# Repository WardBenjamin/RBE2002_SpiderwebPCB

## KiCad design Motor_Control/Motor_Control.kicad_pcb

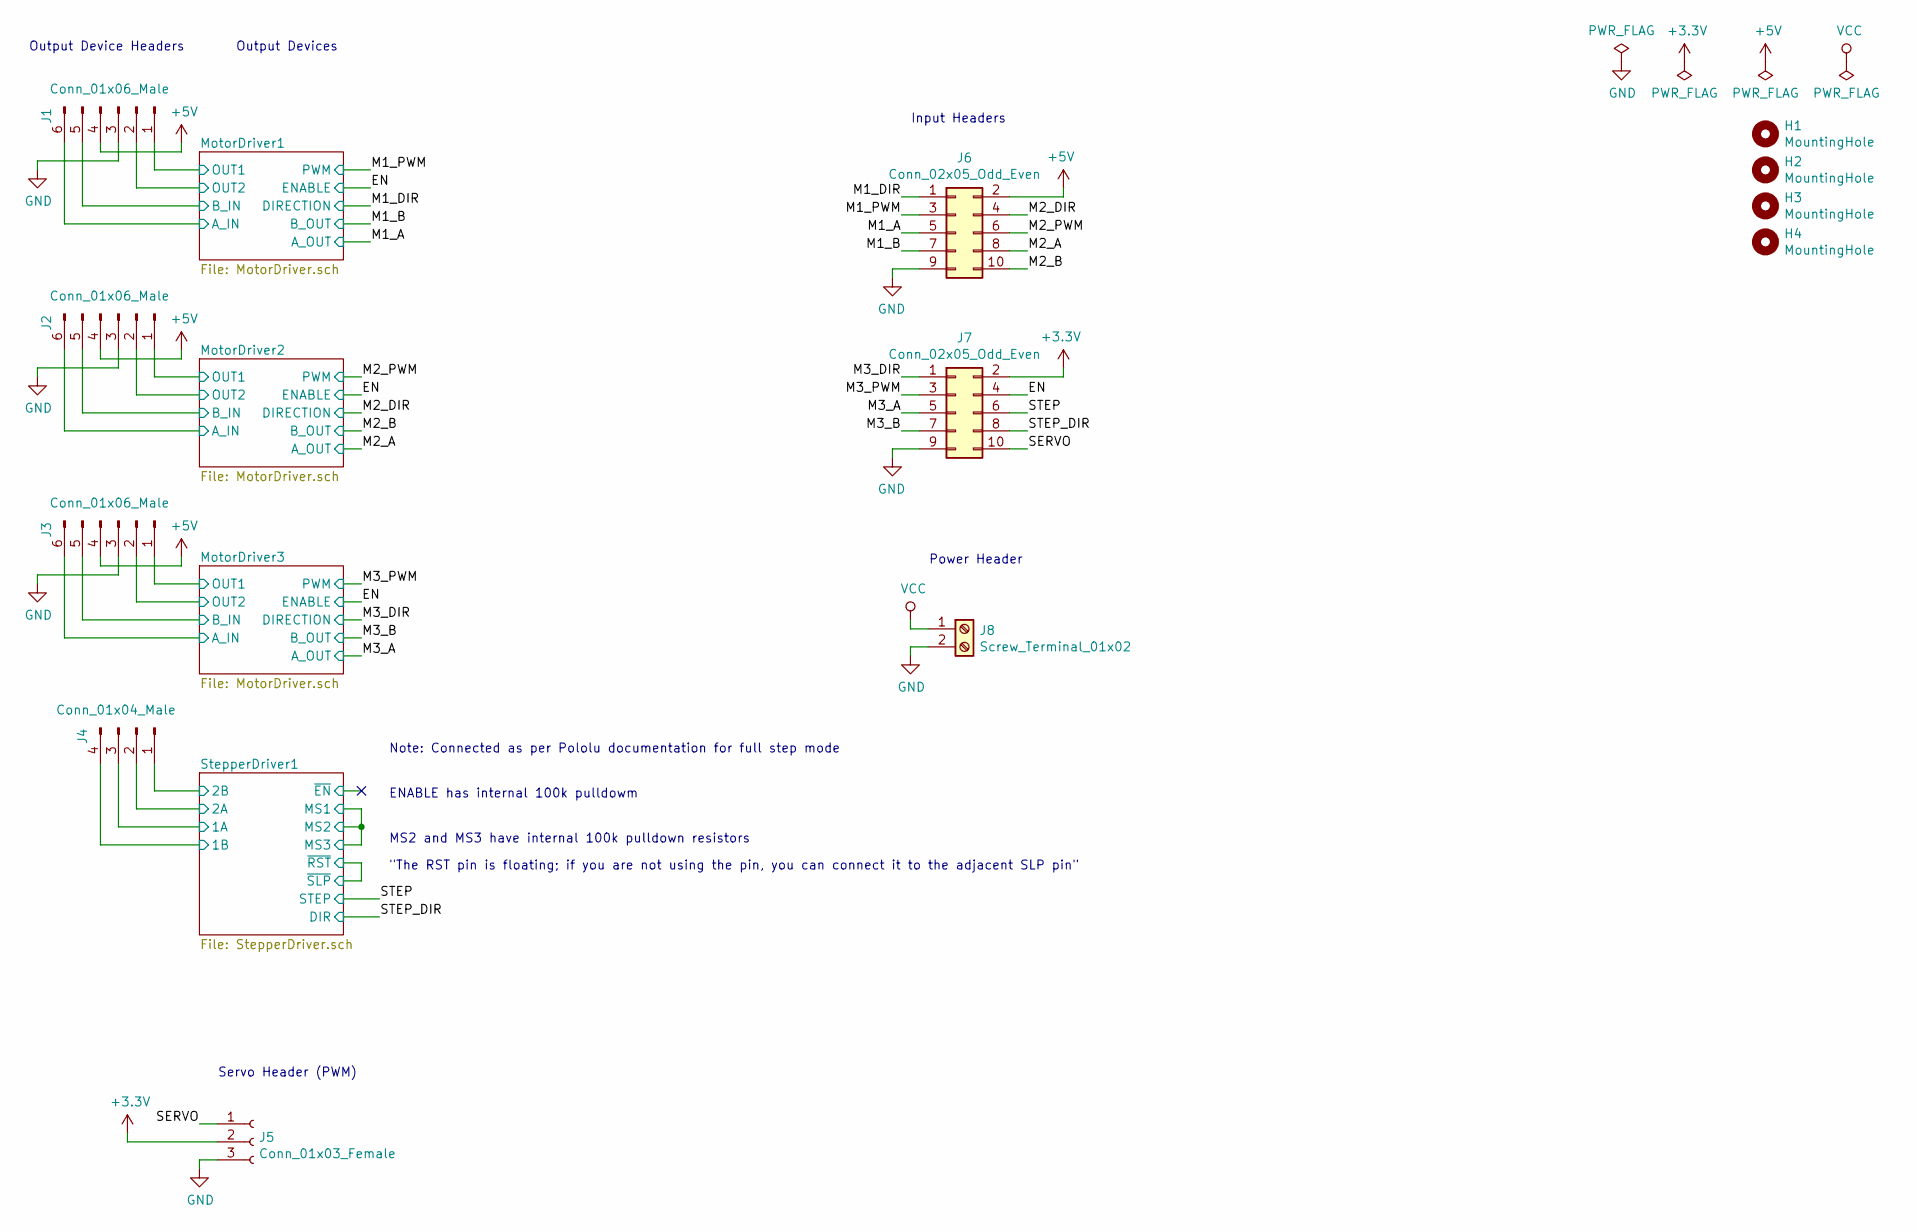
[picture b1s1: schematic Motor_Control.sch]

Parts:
H1, H2, H3, H4: MountingHole; MountingHole_3.2mm_M3
J1, J2, J3: Conn_01x06_Male; PinHeader_1x06_P2.54mm_Vertical
J4: Conn_01x04_Male; PinHeader_1x04_P2.54mm_Vertical
J5: Conn_01x03_Female; PinSocket_1x03_P2.54mm_Vertical
J6, J7: Conn_02x05_Odd_Even; PinSocket_2x05_P2.54mm_Vertical_SMD
J8: Screw_Terminal_01x02; PhoenixContact_MC_1,5_2-G-3.81_1x02_P3.81mm_Horizontal

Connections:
+3V3: J5.2, J7.2; also elsewhere on the board
+5V: J1.4, J2.4, J3.4, J6.2; also elsewhere on the board
/EN: J7.4; also elsewhere on the board
/M1_A: J6.5; also elsewhere on the board
/M1_B: J6.7; also elsewhere on the board
/M1_DIR: J6.1; also elsewhere on the board
/M1_PWM: J6.3; also elsewhere on the board
/M2_A: J6.8; also elsewhere on the board
/M2_B: J6.10; also elsewhere on the board
/M2_DIR: J6.4; also elsewhere on the board
/M2_PWM: J6.6; also elsewhere on the board
/M3_A: J7.5; also elsewhere on the board
/M3_B: J7.7; also elsewhere on the board
/M3_DIR: J7.1; also elsewhere on the board
/M3_PWM: J7.3; also elsewhere on the board
/MotorDriver1/A_IN: J1.6; also elsewhere on the board
/MotorDriver1/B_IN: J1.5; also elsewhere on the board
/MotorDriver1/OUT1: J1.1; also elsewhere on the board
/MotorDriver1/OUT2: J1.2; also elsewhere on the board
/MotorDriver2/A_IN: J2.6; also elsewhere on the board
/MotorDriver2/B_IN: J2.5; also elsewhere on the board
/MotorDriver2/OUT1: J2.1; also elsewhere on the board
/MotorDriver2/OUT2: J2.2; also elsewhere on the board
/MotorDriver3/A_IN: J3.6; also elsewhere on the board
/MotorDriver3/B_IN: J3.5; also elsewhere on the board
/MotorDriver3/OUT1: J3.1; also elsewhere on the board
/MotorDriver3/OUT2: J3.2; also elsewhere on the board
/SERVO: J5.1, J7.10
/STEP: J7.6; also elsewhere on the board
/STEP_DIR: J7.8; also elsewhere on the board
/StepperDriver1/1A: J4.3; also elsewhere on the board
/StepperDriver1/1B: J4.4; also elsewhere on the board
/StepperDriver1/2A: J4.2; also elsewhere on the board
/StepperDriver1/2B: J4.1; also elsewhere on the board
GND: J1.3, J2.3, J3.3, J5.3, J6.9, J7.9, J8.2; also elsewhere on the board
VCC: J8.1; also elsewhere on the board

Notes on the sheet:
ENABLE has internal 100k pulldowm
MS2 and MS3 have internal 100k pulldown resistors
"The RST pin is floating; if you are not using the pin, you can connect it to the adjacent SLP pin"
Output Device Headers
Servo Header (PWM)
Output Devices
Input Headers
Note: Connected as per Pololu documentation for full step mode
Power Header

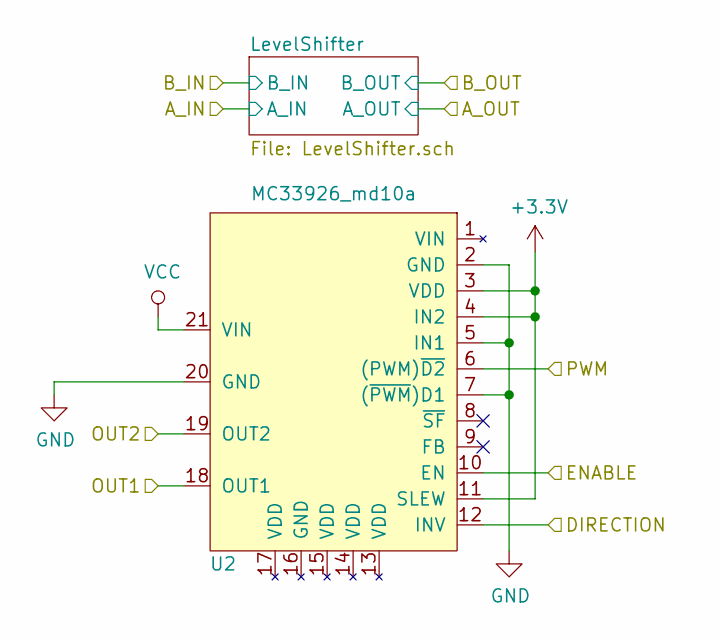
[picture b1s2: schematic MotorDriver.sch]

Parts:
U1: MC33926_md10a

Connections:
+3V3: U1.3 (VDD), U1.4 (IN2), U1.11 (SLEW); also elsewhere on the board
/EN: U1.10 (EN); also elsewhere on the board
/M1_DIR: U1.12 (INV); also elsewhere on the board
/M1_PWM: U1.6 ((PWM)~D2); also elsewhere on the board
/MotorDriver1/OUT1: U1.18 (OUT1); also elsewhere on the board
/MotorDriver1/OUT2: U1.19 (OUT2); also elsewhere on the board
GND: U1.2 (GND), U1.5 (IN1), U1.7 ((~PWM~)D1), U1.20 (GND); also elsewhere on the board
VCC: U1.21 (VIN); also elsewhere on the board

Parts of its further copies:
U2, U3: MC33926_md10a

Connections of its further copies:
+3V3: U2.3 (VDD), U2.4 (IN2), U2.11 (SLEW), U3.3 (VDD), U3.4 (IN2), U3.11 (SLEW); also elsewhere on the board
/EN: U2.10 (EN), U3.10 (EN); also elsewhere on the board
/M2_DIR: U2.12 (INV); also elsewhere on the board
/M2_PWM: U2.6 ((PWM)~D2); also elsewhere on the board
/M3_DIR: U3.12 (INV); also elsewhere on the board
/M3_PWM: U3.6 ((PWM)~D2); also elsewhere on the board
/MotorDriver2/OUT1: U2.18 (OUT1); also elsewhere on the board
/MotorDriver2/OUT2: U2.19 (OUT2); also elsewhere on the board
/MotorDriver3/OUT1: U3.18 (OUT1); also elsewhere on the board
/MotorDriver3/OUT2: U3.19 (OUT2); also elsewhere on the board
GND: U2.2 (GND), U2.5 (IN1), U2.7 ((~PWM~)D1), U2.20 (GND), U3.2 (GND), U3.5 (IN1), U3.7 ((~PWM~)D1), U3.20 (GND); also elsewhere on the board
VCC: U2.21 (VIN), U3.21 (VIN); also elsewhere on the board

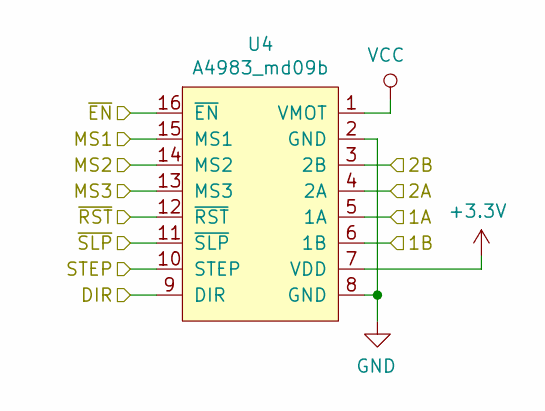
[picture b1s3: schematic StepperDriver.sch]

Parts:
U4: A4983_md09b

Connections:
+3V3: U4.7 (VDD); also elsewhere on the board
/STEP: U4.10 (STEP); also elsewhere on the board
/STEP_DIR: U4.9 (DIR); also elsewhere on the board
/StepperDriver1/1A: U4.5 (1A); also elsewhere on the board
/StepperDriver1/1B: U4.6 (1B); also elsewhere on the board
/StepperDriver1/2A: U4.4 (2A); also elsewhere on the board
/StepperDriver1/2B: U4.3 (2B); also elsewhere on the board
/StepperDriver1/MS1: U4.13 (MS3), U4.14 (MS2), U4.15 (MS1)
/StepperDriver1/~EN: U4.16 (~EN)
/StepperDriver1/~RST: U4.11 (~SLP), U4.12 (~RST)
GND: U4.2 (GND), U4.8 (GND); also elsewhere on the board
VCC: U4.1 (VMOT); also elsewhere on the board

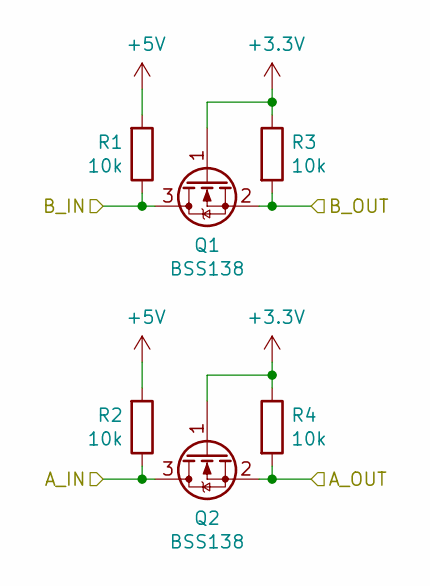
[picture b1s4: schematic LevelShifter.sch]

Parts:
Q1, Q2: BSS138; SOT-23
R1, R2, R3, R4: 10k; R_0603_1608Metric_Pad1.05x0.95mm_HandSolder

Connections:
+3V3: Q1.1 (G), Q2.1 (G), R3.1, R4.1; also elsewhere on the board
+5V: R1.2, R2.2; also elsewhere on the board
/M1_A: Q2.2 (S), R4.2; also elsewhere on the board
/M1_B: Q1.2 (S), R3.2; also elsewhere on the board
/MotorDriver1/A_IN: Q2.3 (D), R2.1; also elsewhere on the board
/MotorDriver1/B_IN: Q1.3 (D), R1.1; also elsewhere on the board

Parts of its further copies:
Q3, Q4, Q5, Q6: BSS138; SOT-23
R5, R6, R7, R8, R9, R10, R11, R12: 10k; R_0603_1608Metric_Pad1.05x0.95mm_HandSolder

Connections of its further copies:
+3V3: Q3.1 (G), Q4.1 (G), Q5.1 (G), Q6.1 (G), R7.1, R8.1, R11.1, R12.1; also elsewhere on the board
+5V: R5.2, R6.2, R9.2, R10.2; also elsewhere on the board
/M2_A: Q4.2 (S), R8.2; also elsewhere on the board
/M2_B: Q3.2 (S), R7.2; also elsewhere on the board
/M3_A: Q6.2 (S), R12.2; also elsewhere on the board
/M3_B: Q5.2 (S), R11.2; also elsewhere on the board
/MotorDriver2/A_IN: Q4.3 (D), R6.1; also elsewhere on the board
/MotorDriver2/B_IN: Q3.3 (D), R5.1; also elsewhere on the board
/MotorDriver3/A_IN: Q6.3 (D), R10.1; also elsewhere on the board
/MotorDriver3/B_IN: Q5.3 (D), R9.1; also elsewhere on the board

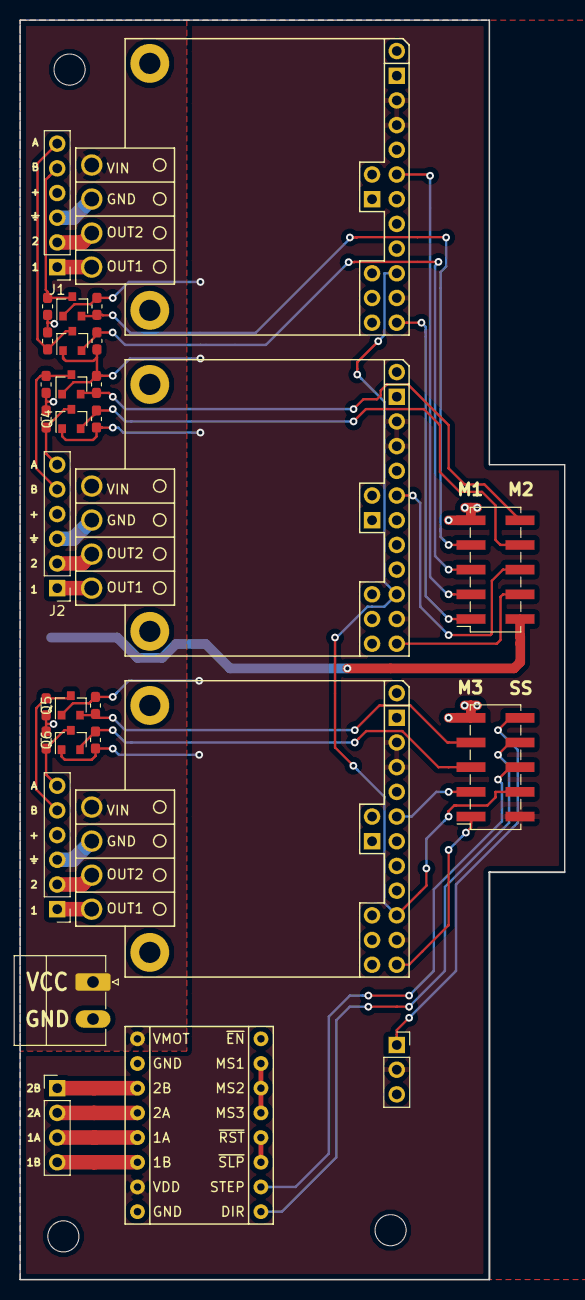
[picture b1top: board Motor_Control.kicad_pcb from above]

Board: 2 copper layers, 56.0 x 129.5 mm, 33 parts (0 on the bottom side), 38 nets.

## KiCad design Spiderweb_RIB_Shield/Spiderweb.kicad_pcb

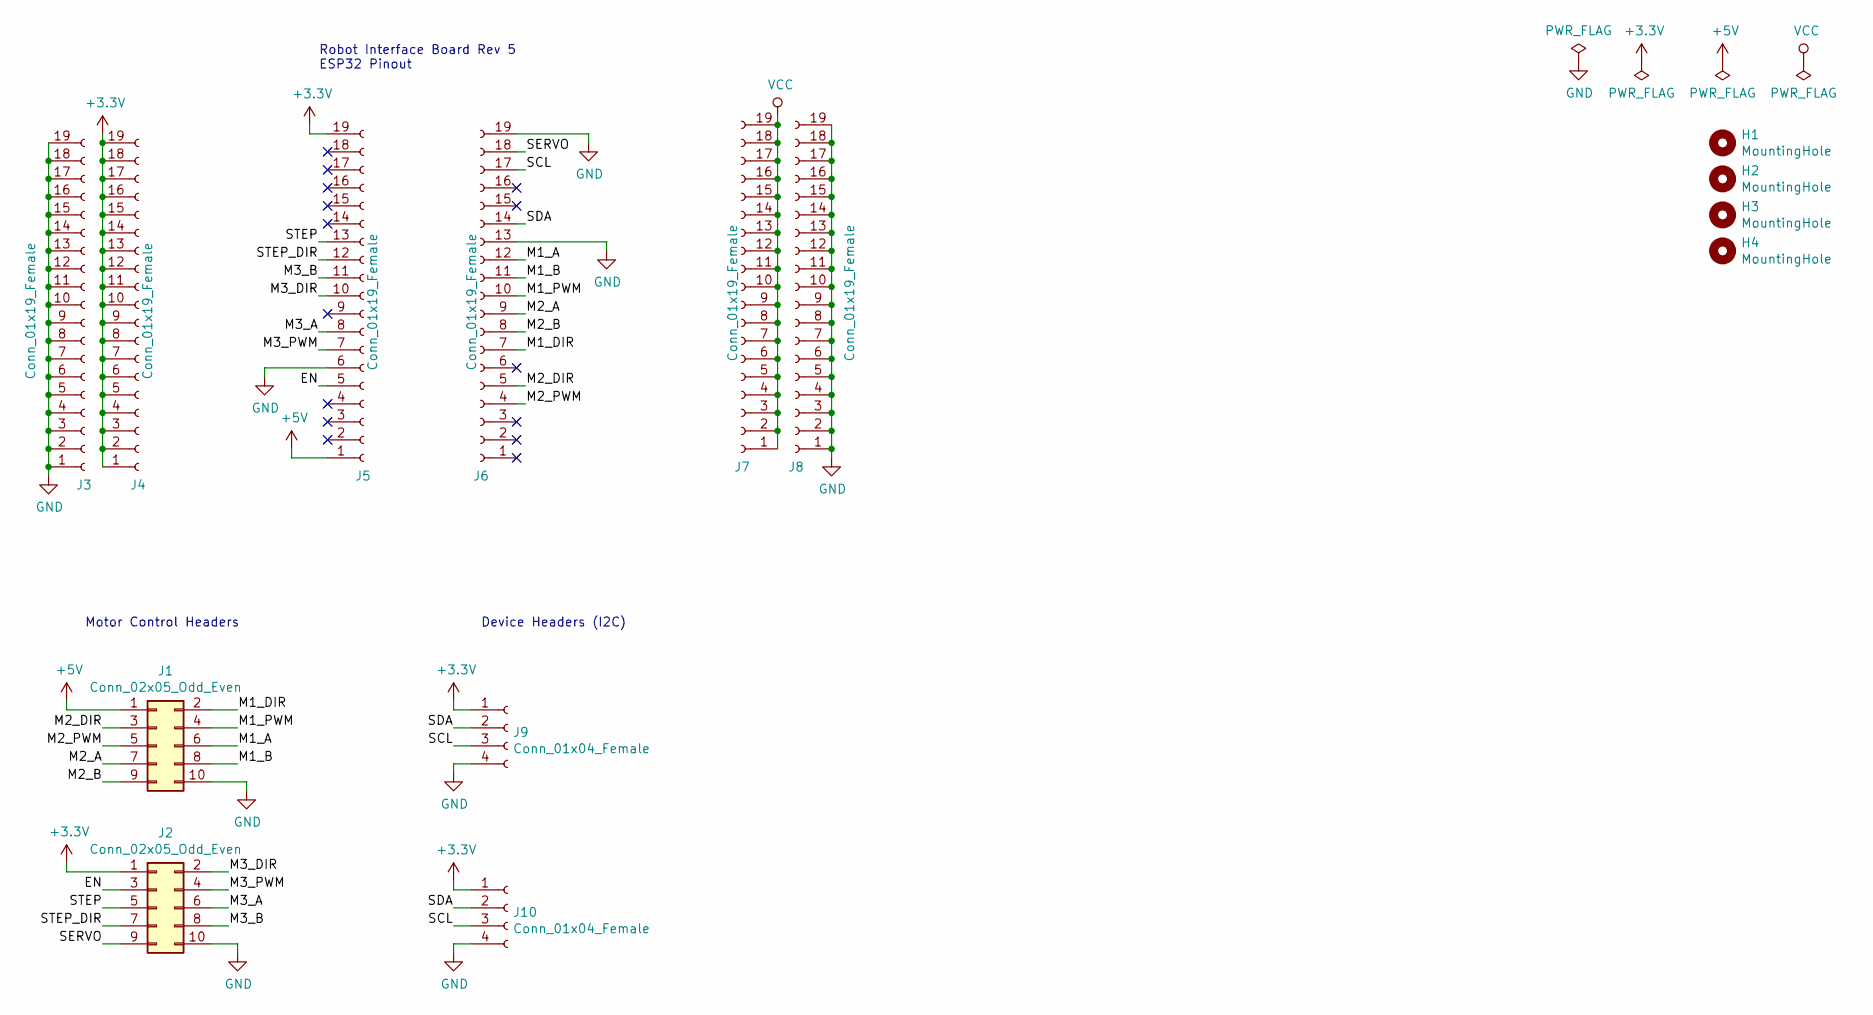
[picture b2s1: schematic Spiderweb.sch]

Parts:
H1, H2, H3, H4: MountingHole; MountingHole_4.3mm_M4
J1, J2: Conn_02x05_Odd_Even; PinHeader_2x05_P2.54mm_Vertical_SMD
J3, J4, J5, J6, J7, J8: Conn_01x19_Female; PinSocket_1x19_P2.54mm_Vertical
J9, J10: Conn_01x04_Female; PinSocket_1x04_P2.54mm_Vertical

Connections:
+3V3: J2.1, J4.1, J4.2, J4.3, J4.4, J4.5, J4.6, J4.7, J4.8, J4.9, J4.10, J4.11, J4.12, J4.13, J4.14, J4.15, J4.16, J4.17, J4.18, J4.19, J5.19, J9.1, J10.1
+5V: J1.1, J5.1
/EN: J2.3, J5.5
/M1_A: J1.6, J6.12
/M1_B: J1.8, J6.11
/M1_DIR: J1.2, J6.7
/M1_PWM: J1.4, J6.10
/M2_A: J1.7, J6.9
/M2_B: J1.9, J6.8
/M2_DIR: J1.3, J6.5
/M2_PWM: J1.5, J6.4
/M3_A: J2.6, J5.8
/M3_B: J2.8, J5.11
/M3_DIR: J2.2, J5.10
/M3_PWM: J2.4, J5.7
/SCL: J6.17, J9.3, J10.3
/SDA: J6.14, J9.2, J10.2
/SERVO: J2.9, J6.18
/STEP: J2.5, J5.13
/STEP_DIR: J2.7, J5.12
GND: J1.10, J2.10, J3.1, J3.2, J3.3, J3.4, J3.5, J3.6, J3.7, J3.8, J3.9, J3.10, J3.11, J3.12, J3.13, J3.14, J3.15, J3.16, J3.17, J3.18, J3.19, J5.6, J6.13, J6.19, J8.1, J8.2, J8.3, J8.4, J8.5, J8.6, J8.7, J8.8, J8.9, J8.10, J8.11, J8.12, J8.13, J8.14, J8.15, J8.16, J8.17, J8.18, J8.19, J9.4, J10.4
VCC: J7.1, J7.2, J7.3, J7.4, J7.5, J7.6, J7.7, J7.8, J7.9, J7.10, J7.11, J7.12, J7.13, J7.14, J7.15, J7.16, J7.17, J7.18, J7.19

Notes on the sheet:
Robot Interface Board Rev 5 ESP32 Pinout
Device Headers (I2C)
Motor Control Headers

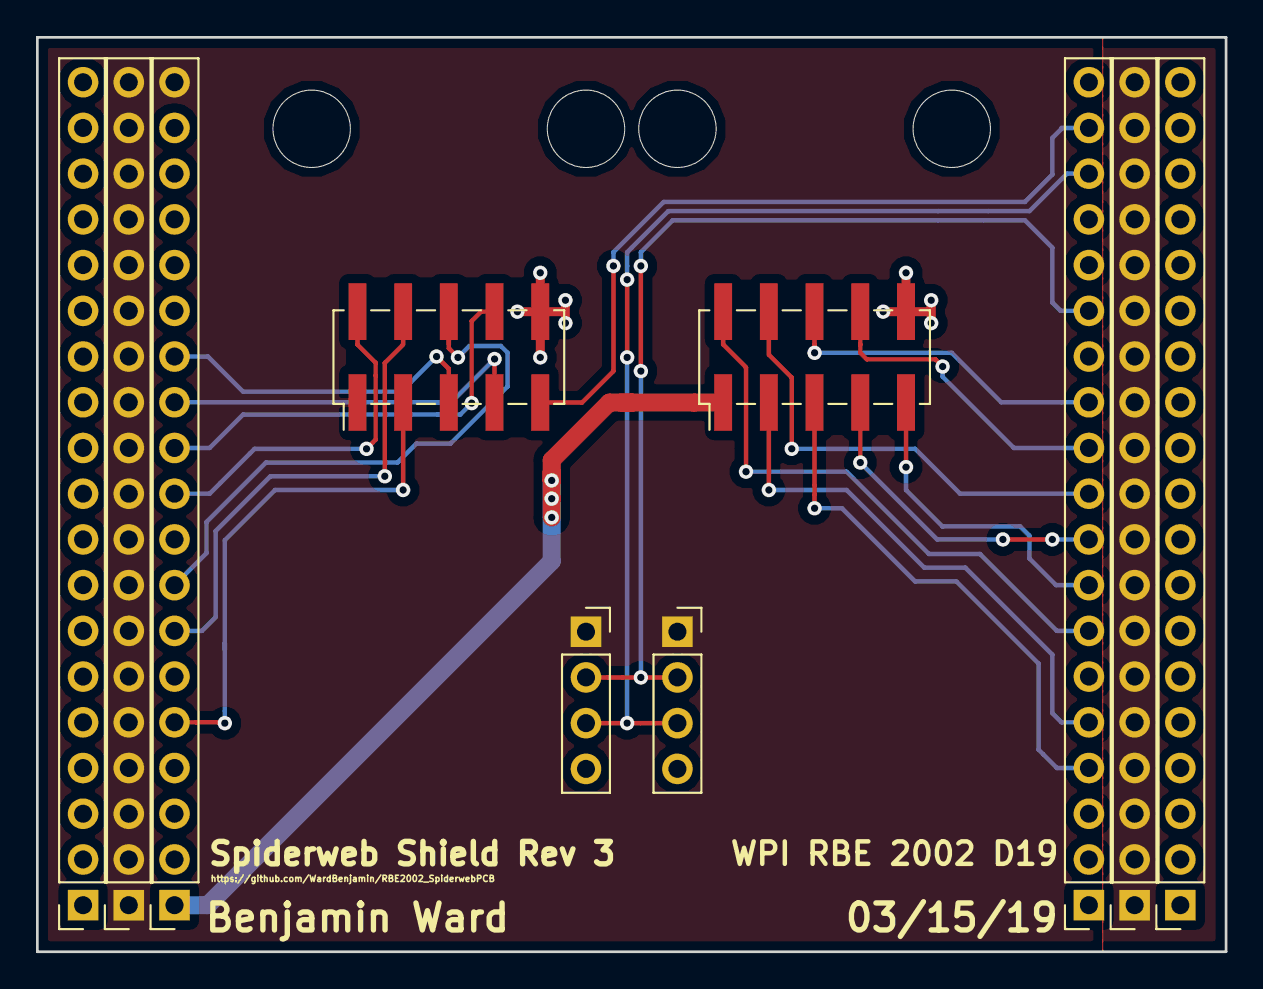
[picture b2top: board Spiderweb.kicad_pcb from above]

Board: 2 copper layers, 66.0 x 50.8 mm, 14 parts (0 on the bottom side), 22 nets.

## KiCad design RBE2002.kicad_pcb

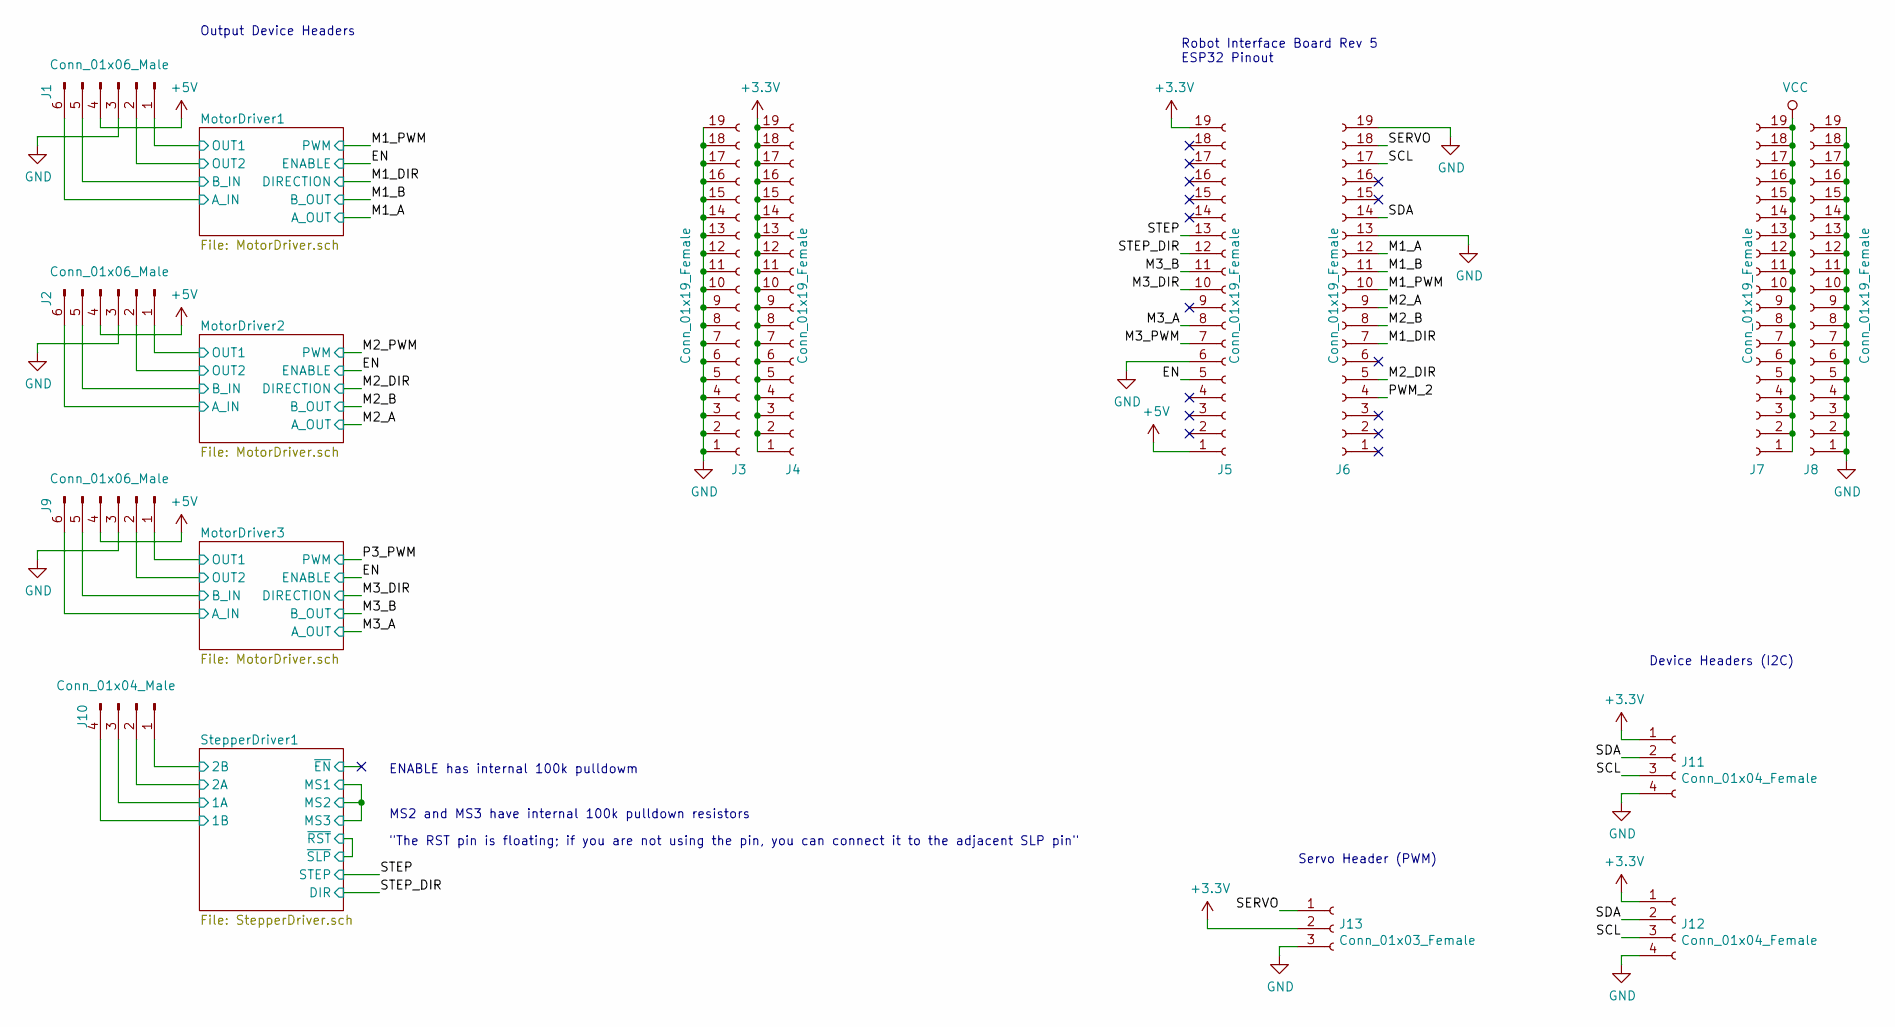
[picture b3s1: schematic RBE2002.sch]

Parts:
J1, J2, J9: Conn_01x06_Male; PinHeader_1x06_P2.54mm_Vertical
J3, J4, J5, J6, J7, J8: Conn_01x19_Female; PinSocket_1x19_P2.54mm_Vertical
J10: Conn_01x04_Male; PinHeader_1x04_P2.54mm_Vertical
J11, J12: Conn_01x04_Female; PinSocket_1x04_P2.54mm_Vertical
J13: Conn_01x03_Female; PinSocket_1x04_P2.54mm_Vertical

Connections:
+3V3: J4.1, J4.2, J4.3, J4.4, J4.5, J4.6, J4.7, J4.8, J4.9, J4.10, J4.11, J4.12, J4.13, J4.14, J4.15, J4.16, J4.17, J4.18, J4.19, J5.19, J11.1, J12.1, J13.2; also elsewhere on the board
+5V: J1.4, J2.4, J5.1, J9.4; also elsewhere on the board
/EN: J5.5; also elsewhere on the board
/M1_A: J6.12; also elsewhere on the board
/M1_B: J6.11; also elsewhere on the board
/M1_DIR: J6.7; also elsewhere on the board
/M1_PWM: J6.10; also elsewhere on the board
/M2_A: J6.9; also elsewhere on the board
/M2_B: J6.8; also elsewhere on the board
/M2_DIR: J6.5; also elsewhere on the board
/M3_A: J5.8; also elsewhere on the board
/M3_B: J5.11; also elsewhere on the board
/M3_DIR: J5.10; also elsewhere on the board
/M3_PWM: J5.7
/MotorDriver1/A_IN: J1.6; also elsewhere on the board
/MotorDriver1/B_IN: J1.5; also elsewhere on the board
/MotorDriver1/OUT1: J1.1; also elsewhere on the board
/MotorDriver1/OUT2: J1.2; also elsewhere on the board
/MotorDriver2/A_IN: J2.6; also elsewhere on the board
/MotorDriver2/B_IN: J2.5; also elsewhere on the board
/MotorDriver2/OUT1: J2.1; also elsewhere on the board
/MotorDriver2/OUT2: J2.2; also elsewhere on the board
/MotorDriver3/A_IN: J9.6; also elsewhere on the board
/MotorDriver3/B_IN: J9.5; also elsewhere on the board
/MotorDriver3/OUT1: J9.1; also elsewhere on the board
/MotorDriver3/OUT2: J9.2; also elsewhere on the board
/PWM_2: J6.4
/SCL: J6.17, J11.3, J12.3
/SDA: J6.14, J11.2, J12.2
/SERVO: J6.18, J13.1
/STEP: J5.13; also elsewhere on the board
/STEP_DIR: J5.12; also elsewhere on the board
/StepperDriver1/1A: J10.3; also elsewhere on the board
/StepperDriver1/1B: J10.4; also elsewhere on the board
/StepperDriver1/2A: J10.2; also elsewhere on the board
/StepperDriver1/2B: J10.1; also elsewhere on the board
GND: J1.3, J2.3, J3.1, J3.2, J3.3, J3.4, J3.5, J3.6, J3.7, J3.8, J3.9, J3.10, J3.11, J3.12, J3.13, J3.14, J3.15, J3.16, J3.17, J3.18, J3.19, J5.6, J6.13, J6.19, J8.1, J8.2, J8.3, J8.4, J8.5, J8.6, J8.7, J8.8, J8.9, J8.10, J8.11, J8.12, J8.13, J8.14, J8.15, J8.16, J8.17, J8.18, J8.19, J9.3, J11.4, J12.4, J13.3; also elsewhere on the board
VCC: J7.1, J7.2, J7.3, J7.4, J7.5, J7.6, J7.7, J7.8, J7.9, J7.10, J7.11, J7.12, J7.13, J7.14, J7.15, J7.16, J7.17, J7.18, J7.19; also elsewhere on the board

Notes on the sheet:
Robot Interface Board Rev 5 ESP32 Pinout
ENABLE has internal 100k pulldowm
MS2 and MS3 have internal 100k pulldown resistors
"The RST pin is floating; if you are not using the pin, you can connect it to the adjacent SLP pin"
Device Headers (I2C)
Output Device Headers
Servo Header (PWM)

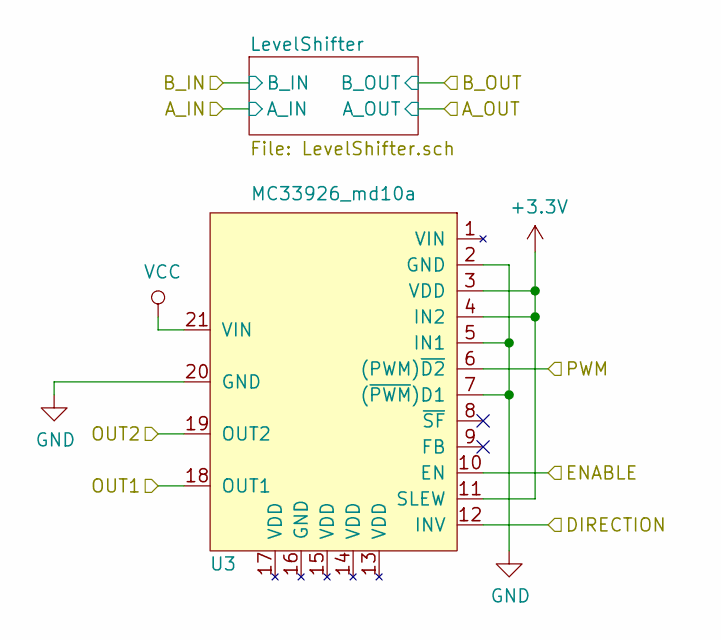
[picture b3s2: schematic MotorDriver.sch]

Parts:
U1: MC33926_md10a

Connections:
+3V3: U1.3 (VDD), U1.4 (IN2), U1.11 (SLEW); also elsewhere on the board
/EN: U1.10 (EN); also elsewhere on the board
/M1_DIR: U1.12 (INV); also elsewhere on the board
/M1_PWM: U1.6 ((PWM)~D2); also elsewhere on the board
/MotorDriver1/OUT1: U1.18 (OUT1); also elsewhere on the board
/MotorDriver1/OUT2: U1.19 (OUT2); also elsewhere on the board
GND: U1.2 (GND), U1.5 (IN1), U1.7 ((~PWM~)D1), U1.20 (GND); also elsewhere on the board
VCC: U1.21 (VIN); also elsewhere on the board

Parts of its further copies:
U2, U3: MC33926_md10a

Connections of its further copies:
+3V3: U2.3 (VDD), U2.4 (IN2), U2.11 (SLEW), U3.3 (VDD), U3.4 (IN2), U3.11 (SLEW); also elsewhere on the board
/EN: U2.10 (EN), U3.10 (EN); also elsewhere on the board
/M2_DIR: U2.12 (INV); also elsewhere on the board
/M2_PWM: U2.6 ((PWM)~D2)
/M3_DIR: U3.12 (INV); also elsewhere on the board
/MotorDriver2/OUT1: U2.18 (OUT1); also elsewhere on the board
/MotorDriver2/OUT2: U2.19 (OUT2); also elsewhere on the board
/MotorDriver3/OUT1: U3.18 (OUT1); also elsewhere on the board
/MotorDriver3/OUT2: U3.19 (OUT2); also elsewhere on the board
/P3_PWM: U3.6 ((PWM)~D2)
GND: U2.2 (GND), U2.5 (IN1), U2.7 ((~PWM~)D1), U2.20 (GND), U3.2 (GND), U3.5 (IN1), U3.7 ((~PWM~)D1), U3.20 (GND); also elsewhere on the board
VCC: U2.21 (VIN), U3.21 (VIN); also elsewhere on the board

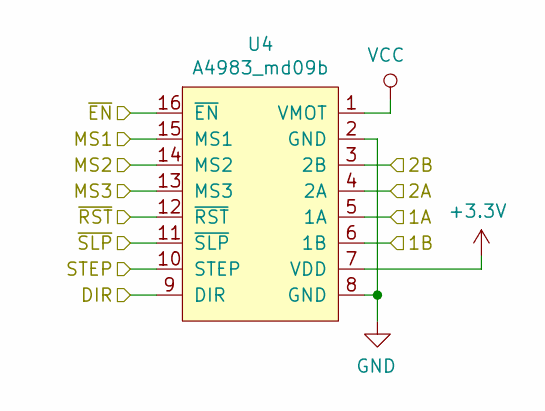
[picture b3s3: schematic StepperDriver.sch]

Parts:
U4: A4983_md09b

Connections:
+3V3: U4.7 (VDD); also elsewhere on the board
/STEP: U4.10 (STEP); also elsewhere on the board
/STEP_DIR: U4.9 (DIR); also elsewhere on the board
/StepperDriver1/1A: U4.5 (1A); also elsewhere on the board
/StepperDriver1/1B: U4.6 (1B); also elsewhere on the board
/StepperDriver1/2A: U4.4 (2A); also elsewhere on the board
/StepperDriver1/2B: U4.3 (2B); also elsewhere on the board
/StepperDriver1/MS1: U4.13 (MS3), U4.14 (MS2), U4.15 (MS1)
/StepperDriver1/~EN: U4.16 (~EN)
/StepperDriver1/~RST: U4.11 (~SLP), U4.12 (~RST)
GND: U4.2 (GND), U4.8 (GND); also elsewhere on the board
VCC: U4.1 (VMOT); also elsewhere on the board

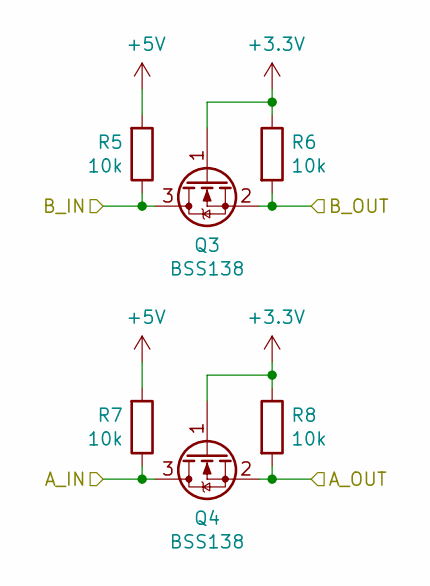
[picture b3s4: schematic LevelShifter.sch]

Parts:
Q1, Q2: BSS138; SOT-23
R1, R2, R3, R4: 10k; R_0603_1608Metric_Pad1.05x0.95mm_HandSolder

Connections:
+3V3: Q1.1 (G), Q2.1 (G), R2.1, R4.1; also elsewhere on the board
+5V: R1.2, R3.2; also elsewhere on the board
/M1_A: Q2.2 (S), R4.2; also elsewhere on the board
/M1_B: Q1.2 (S), R2.2; also elsewhere on the board
/MotorDriver1/A_IN: Q2.3 (D), R3.1; also elsewhere on the board
/MotorDriver1/B_IN: Q1.3 (D), R1.1; also elsewhere on the board

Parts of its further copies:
Q3, Q4, Q5, Q6: BSS138; SOT-23
R5, R6, R7, R8, R9, R10, R11, R12: 10k; R_0603_1608Metric_Pad1.05x0.95mm_HandSolder

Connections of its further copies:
+3V3: Q3.1 (G), Q4.1 (G), Q5.1 (G), Q6.1 (G), R6.1, R8.1, R10.1, R12.1; also elsewhere on the board
+5V: R5.2, R7.2, R9.2, R11.2; also elsewhere on the board
/M2_A: Q4.2 (S), R8.2; also elsewhere on the board
/M2_B: Q3.2 (S), R6.2; also elsewhere on the board
/M3_A: Q6.2 (S), R12.2; also elsewhere on the board
/M3_B: Q5.2 (S), R10.2; also elsewhere on the board
/MotorDriver2/A_IN: Q4.3 (D), R7.1; also elsewhere on the board
/MotorDriver2/B_IN: Q3.3 (D), R5.1; also elsewhere on the board
/MotorDriver3/A_IN: Q6.3 (D), R11.1; also elsewhere on the board
/MotorDriver3/B_IN: Q5.3 (D), R9.1; also elsewhere on the board

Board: 2 copper layers, 35 parts (0 on the bottom side), 38 nets, no tracks yet.

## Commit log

2019-03-14 Rev 1 (unfinished)
2019-03-16 Split Spiderweb and Motor Control boards
2019-03-18 Update layout files
